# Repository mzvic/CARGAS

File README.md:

# CARGAS

This repository contains Python scripts designed for the CARGAS LLAMA Project. The main.py script provides real-time monitoring and plotting of temperature data from a PT100 sensor connected to a FPGA with an ADC1 Module. 
graph.py provides the analysis of historical temperature data stored in a file.

# Usage (Laboratory's Settings)

## main.py
Connect the FPGA to the pc and run the script with:
```
python3 main.py
```
The script will prompt you for two options:
    
    - Save data (`opt_save`): Enter 'y' to save data, or 'n' to skip saving.
    - Average data (`opt_avg`): Enter 'y' to plot the average data, or 'n' to plot raw data.
The script will continuously read data from the FPGA and display real-time plots. If saving is enabled, data will be appended to a file named with the time when you execute the script.

 To stop the script and close the plot, press `Ctrl+C` in the terminal where the script is running.
 > **Note:** Make sure to change the **comms.setPort()** argument to your port where the FPGA is connected. /dev/ttyUSB1 is the default for linux.
 ## graph.py
 Ensure that your temperature data is stored in a CSV file with three columns 
  ```
 BITS,VOLTAGE,TEMPERATURE 
  ```
 Then run the script with:
 ```
python3 graph.py path/to/your/datafile.txt
```
 Replace  *path/to/your/datafile.txt*  with the path to your actual file.
 The script will analyze the temperature data and generate a plot displaying the temperature readings over time.
 Statistical information will be included in the legend of the plot, providing details such as **mean temperature**, **coefficient of variation**, **number of samples**, **number of peaks**, and **temperature range**.
 > **Note:** To change the threshold of the peaks, change the **line 19** in the code with the values that you prefer.

## FPGA
Make sure to connect the ADC1 Module in the top JD connector. The FPGA contains in their memory the code to provide the data from a A0 data connected to de ADC1.

# Dependencies

- main.py requires matplotlib pyserial numpy (pip3 install matplotlib pyserial numpy)
- graph.py requires matplotlib numpy (pip3 install matplotlib numpy)

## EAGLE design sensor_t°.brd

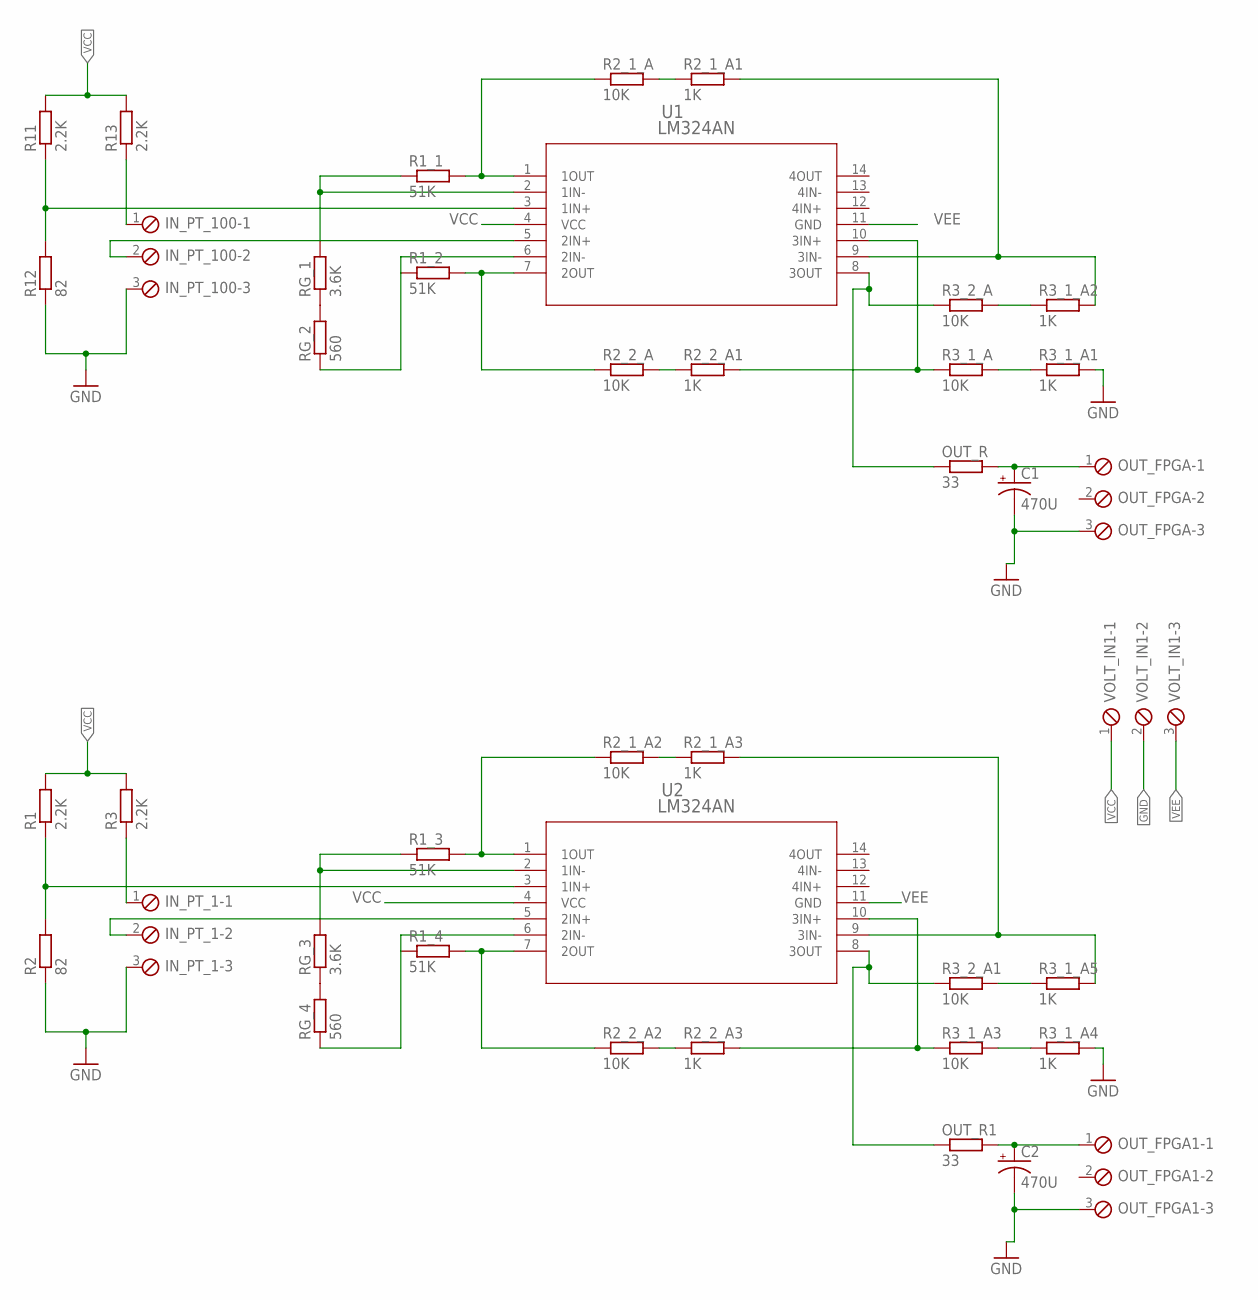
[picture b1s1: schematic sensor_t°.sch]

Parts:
C1, C2: 470U; TAP5-80
IN_PT_1, IN_PT_100: MPT3; 3POL254
OUT_FPGA, OUT_FPGA1: MPT3; 3POL254
OUT_R, OUT_R1: 33; 0207/10
R1, R3, R11, R13: 2.2K; 0207/10
R1_1, R1_2, R1_3, R1_4: 51K; 0207/10
R2, R12: 82; 0207/10
R2_1_A, R2_1_A2, R2_2_A, R2_2_A2, R3_1_A, R3_1_A3, R3_2_A, R3_2_A1: 10K; 0207/10
R2_1_A1, R2_1_A3, R2_2_A1, R2_2_A3, R3_1_A1, R3_1_A2, R3_1_A4, R3_1_A5: 1K; 0207/10
RG_1, RG_3: 3.6K; 0207/10
RG_2, RG_4: 560; 0207/10
U1, U2: LM324AN; N14
VOLT_IN1: MPT3; 3POL254

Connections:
GND: C1.-, C2.-, IN_PT_1.3, IN_PT_100.3, OUT_FPGA.3, OUT_FPGA1.3, R2.1, R3_1_A1.2, R3_1_A4.2, R12.1, VOLT_IN1.2
unnamed: R11.1, R12.2, U1.3 (1IN+)
unnamed: IN_PT_100.1, R13.1
unnamed: RG_1.1, RG_2.2
unnamed: R1_1.2, R2_1_A.1, U1.1 (1OUT)
unnamed: R2_1_A.2, R2_1_A1.1
unnamed: R2_1_A1.2, R3_1_A2.2, U1.9 (3IN-)
unnamed: R1_2.2, R2_2_A.1, U1.7 (2OUT)
unnamed: R1_1.1, RG_1.2, U1.2 (1IN-)
unnamed: R1_2.1, RG_2.1, U1.6 (2IN-)
unnamed: R2_2_A.2, R2_2_A1.1
unnamed: R2_2_A1.2, R3_1_A.1, U1.10 (3IN+)
unnamed: OUT_R.1, R3_2_A.1, U1.8 (3OUT)
unnamed: R3_1_A2.1, R3_2_A.2
unnamed: R3_1_A.2, R3_1_A1.1
unnamed: C1.+, OUT_FPGA.1, OUT_R.2
unnamed: IN_PT_100.2, U1.5 (2IN+)
unnamed: RG_3.1, RG_4.2
unnamed: R1_3.2, R2_1_A2.1, U2.1 (1OUT)
unnamed: R2_1_A2.2, R2_1_A3.1
unnamed: R2_1_A3.2, R3_1_A5.2, U2.9 (3IN-)
unnamed: R1_3.1, RG_3.2, U2.2 (1IN-)
unnamed: R1_4.2, R2_2_A2.1, U2.7 (2OUT)
unnamed: R1_4.1, RG_4.1, U2.6 (2IN-)
unnamed: R2_2_A2.2, R2_2_A3.1
unnamed: R2_2_A3.2, R3_1_A3.1, U2.10 (3IN+)
unnamed: OUT_R1.1, R3_2_A1.1, U2.8 (3OUT)
unnamed: R3_1_A5.1, R3_2_A1.2
unnamed: R3_1_A3.2, R3_1_A4.1
unnamed: C2.+, OUT_FPGA1.1, OUT_R1.2
unnamed: R1.1, R2.2, U2.3 (1IN+)
unnamed: IN_PT_1.1, R3.1
unnamed: IN_PT_1.2, U2.5 (2IN+)
VCC: R1.2, R3.2, R11.2, R13.2, U1.4 (VCC), U2.4 (VCC), VOLT_IN1.1
VEE: U1.11 (GND), U2.11 (GND), VOLT_IN1.3

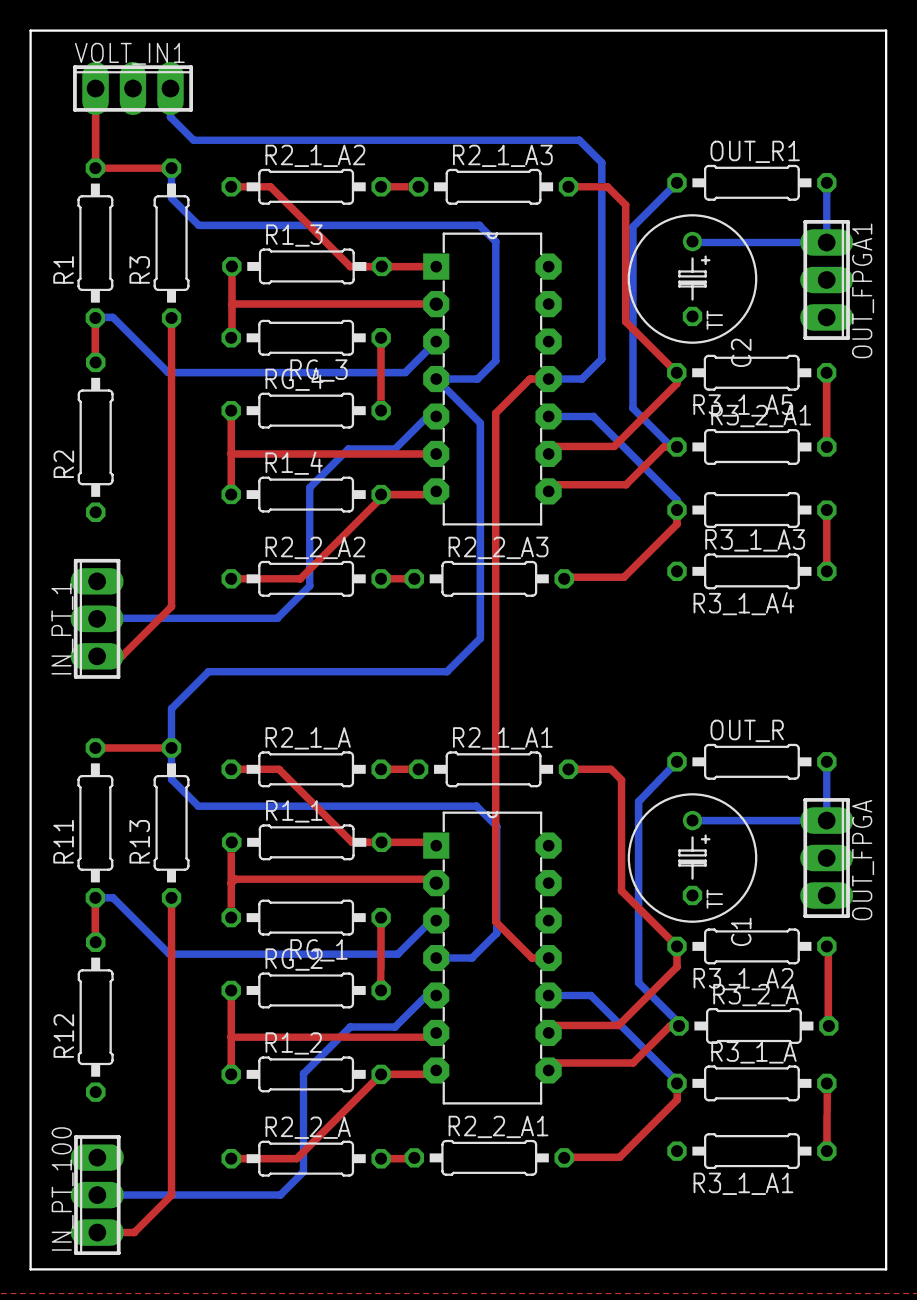
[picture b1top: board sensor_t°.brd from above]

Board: 2 copper layers, 58.0 x 84.0 mm, 41 parts (0 on the bottom side), 35 nets.

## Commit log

2023-11-25 added xpr and gui and to do
2023-12-01 fail reading
2023-12-04 main only read and graph
2023-12-04 main saving data
2023-12-05 current working
2023-12-06 updating lakeshore comm
2023-12-07 uploading
2023-12-09 status: working on gui
2023-12-09 irrelevant vivado stuff
2023-12-11 cristian aprende github
2023-12-11 last before calibration
2023-12-12 cleaning
2023-12-12 cache
2023-12-12 adding daya
2023-12-13 war is over
2023-12-13 preparing ui
2023-12-13 todo: establecer conexion con grafica y fpg
2023-12-20 all working
2024-01-04 adding calibration script
2024-01-05 select com port added to main
2024-01-05 added tomas
2024-01-09 finishing
2024-01-09 fix CAL1y2.txt
2024-01-16 adding calibration files and pcb files
2024-01-18 adding both ports
2024-02-12 Documento Informativo v0.1

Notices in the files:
parts and their libraries:
COPYRIGHT: Copyright (C) 2023 Ultra Librarian. All rights reserved.
